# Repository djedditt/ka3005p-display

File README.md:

# ka3005p-display

This repository contains a KiCad project for a Korad KA3005P display driver, included are the schematic, pcb layout and gerber files. This board can replace the existing KA002_V3.x PCB in a Korad KA3005P (or KA3005D) power supply.

## Table of Contents

* [Bill of Materials (BOM)](#bom)
* [Pictures](#pictures)
* [License](#license)
* [Contact](#contact)

## Bill of Materials (BOM)

Below you'll find the bill of materials for this board. The original PCB comes with 4.0mm LEDs, but I went for 5.0mm because those are more readily available.

| ID | Designator | Description | Quantity |
|---|---|---|---|
|1|C1|Capacitor, Ceramic, 22uF, 25V, 10%, X7R, 0805|1|
|2|LED1, LED2|4-Digit 7-Segment LED Display, Red, Common Cathode, TH, 0.40"|2|
|3|R17, R18, R19, R20, R21|Resistor, 1k Ohm, 1%, 1/8 W, 0805|5|
|4|Q4, Q5, Q6, Q7, Q8|NPN Transistor, MMBT3904, SOT-23-3|5|
|5|D1, D2, D3, D4, D5, D6, D7, D8, D9, D10|LED, Red, TH, 4.0mm (or 5.0mm)|10|
|6|U18|Low Dropout Linear Regulator, AZ1117-3.3, SOT-223|1|
|7|R1, R2, R3, R4, R5, R6, R7, R8, R9, R10, R11, R12, R13, R14, R15, R16|Resistor, 330 Ohm, 5%, 1/4 W, 0805|16
|8|U1, U3| 8-Bit Shift Register, 74HC595, SOIC-16|2
|9|CON1| Female Header, 12-Pin (2x6), 2.54mm|1

## Pictures

The finished board:

Bare PCB (front and back):

## License

This work is licensed under a [Creative Commons Attribution 4.0 International
License][cc-by].

[cc-by]: http://creativecommons.org/licenses/by/4.0/ 

## Contact

You can e-mail me at: ![email-address]

[email-address]: https://djedditt.net/github/email-address.gif

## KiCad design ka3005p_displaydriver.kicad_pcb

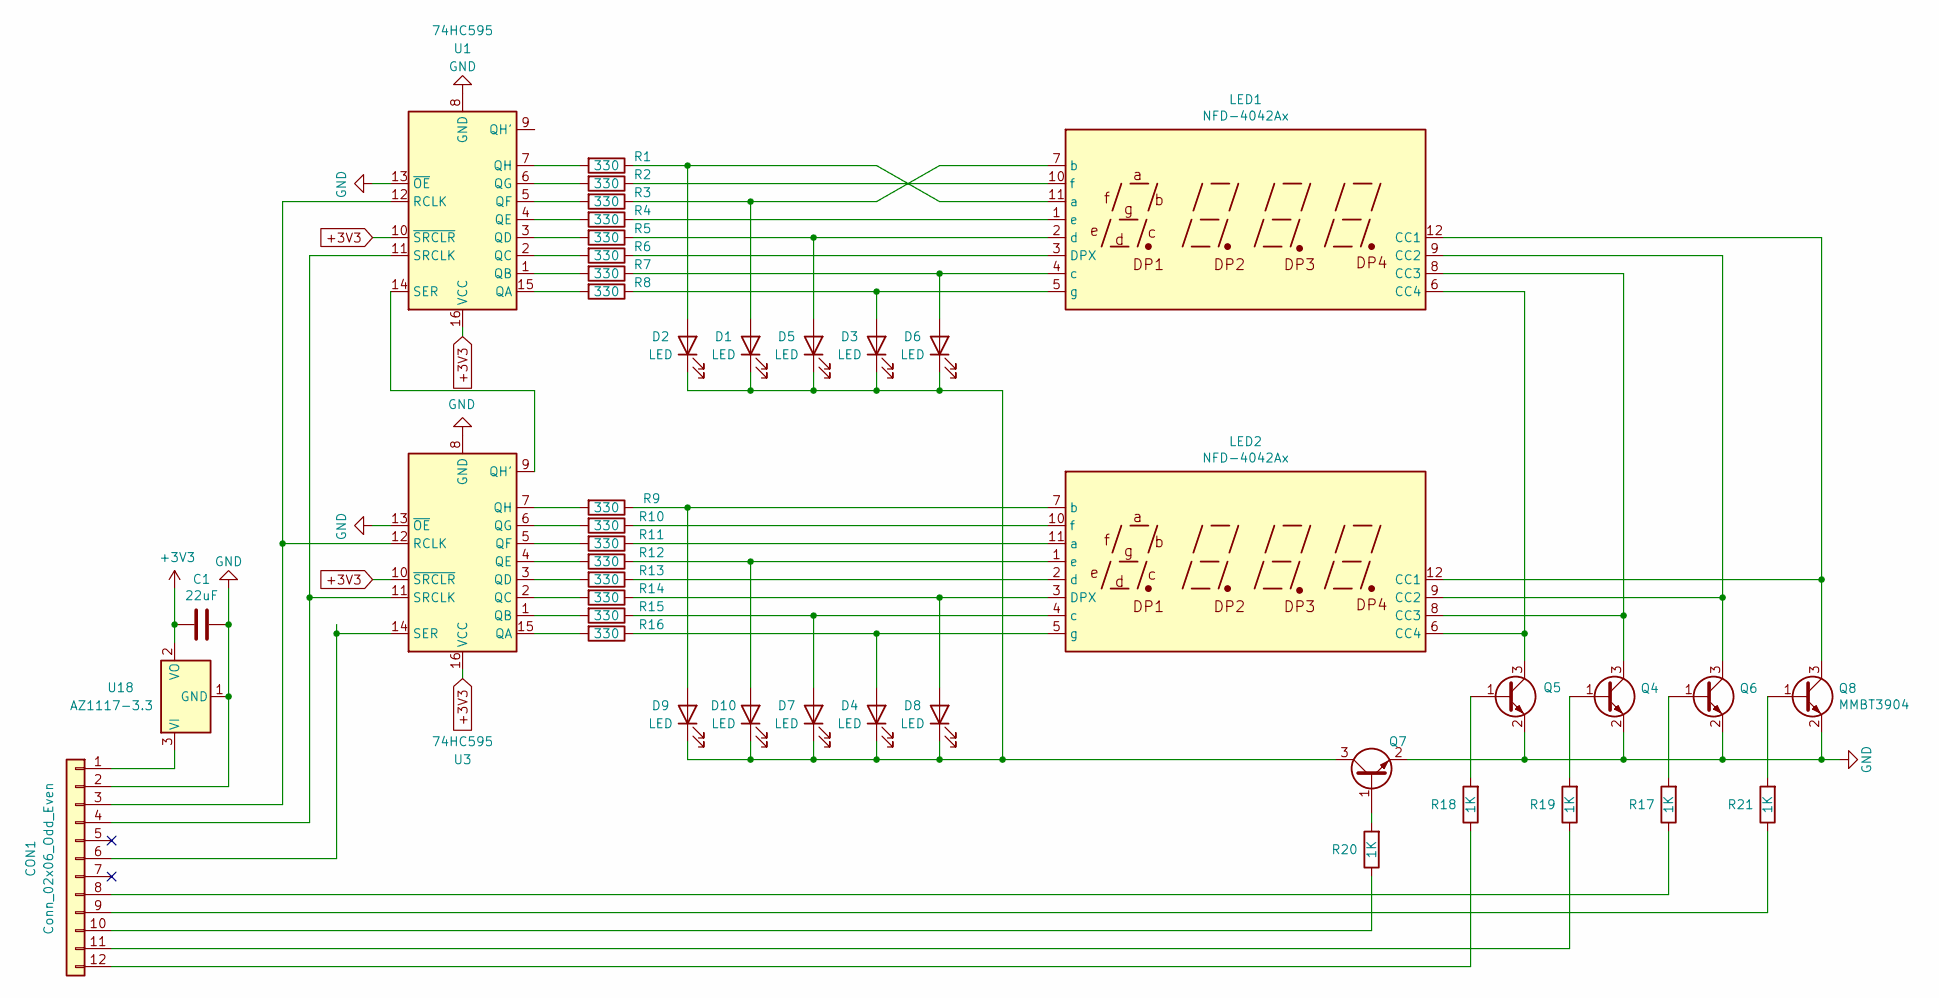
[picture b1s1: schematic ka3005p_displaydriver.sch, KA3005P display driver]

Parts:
C1: 22uF; C_0805_2012Metric_Pad1.15x1.40mm_HandSolder
CON1: Conn_02x06_Odd_Even; PinSocket_2x06_P2.54mm_Vertical
D1, D2, D3, D4, D5, D6, D7, D8, D9, D10: LED; LED_D4.0mm
LED1, LED2: NFD-4042Ax
Q4, Q5, Q6, Q7, Q8: MMBT3904; SOT-23
R1, R2, R3, R4, R5, R6, R7, R8, R9, R10, R11, R12, R13, R14, R15, R16: 330; R_0805_2012Metric_Pad1.15x1.40mm_HandSolder
R17, R18, R19, R20, R21: 1K; R_0805_2012Metric_Pad1.15x1.40mm_HandSolder
U1, U3: 74HC595; SOIC-16_3.9x9.9mm_P1.27mm
U18: AZ1117-3.3; SOT-223

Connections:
+3V3: C1.2, U1.10 (~SRCLR), U1.16 (VCC), U3.10 (~SRCLR), U3.16 (VCC), U18.2 (VO), U18.4
GND: C1.1, CON1.2, Q4.2 (E), Q5.2 (E), Q6.2 (E), Q7.2 (E), Q8.2 (E), U1.8 (GND), U1.13 (~OE), U3.8 (GND), U3.13 (~OE), U18.1 (GND)
unnamed: CON1.1, U18.3 (VI)
unnamed: CON1.3, U1.12 (RCLK), U3.12 (RCLK)
unnamed: CON1.4, U1.11 (SRCLK), U3.11 (SRCLK)
unnamed: CON1.6, U3.14 (SER)
unnamed: CON1.8, R17.1
unnamed: CON1.9, R21.1
unnamed: CON1.10, R20.1
unnamed: CON1.11, R19.1
unnamed: CON1.12, R18.1
unnamed: D1.1 (K), D2.1 (K), D3.1 (K), D4.1 (K), D5.1 (K), D6.1 (K), D7.1 (K), D8.1 (K), D9.1 (K), D10.1 (K), Q7.3 (C)
unnamed: D1.2 (A), LED1.7 (b), R3.1
unnamed: D2.2 (A), LED1.11 (a), R1.1
unnamed: D3.2 (A), LED1.5 (g), R8.1
unnamed: D4.2 (A), LED2.5 (g), R16.1
unnamed: D5.2 (A), LED1.2 (d), R5.1
unnamed: D6.2 (A), LED1.4 (c), R7.1
unnamed: D7.2 (A), LED2.4 (c), R15.1
unnamed: D8.2 (A), LED2.3 (DPX), R14.1
unnamed: D9.2 (A), LED2.7 (b), R9.1
unnamed: D10.2 (A), LED2.1 (e), R12.1
unnamed: LED1.1 (e), R4.1
unnamed: LED1.3 (DPX), R6.1
unnamed: LED1.6 (CC4), LED2.6 (CC4), Q5.3 (C)
unnamed: LED1.8 (CC3), LED2.8 (CC3), Q4.3 (C)
unnamed: LED1.9 (CC2), LED2.9 (CC2), Q6.3 (C)
unnamed: LED1.10 (f), R2.1
unnamed: LED1.12 (CC1), LED2.12 (CC1), Q8.3 (C)
unnamed: LED2.2 (d), R13.1
unnamed: LED2.10 (f), R10.1
unnamed: LED2.11 (a), R11.1
unnamed: Q4.1 (B), R19.2
unnamed: Q5.1 (B), R18.2
unnamed: Q6.1 (B), R17.2
unnamed: Q7.1 (B), R20.2
unnamed: Q8.1 (B), R21.2
unnamed: R1.2, U1.7 (QH)
unnamed: R2.2, U1.6 (QG)
unnamed: R3.2, U1.5 (QF)
unnamed: R4.2, U1.4 (QE)
unnamed: R5.2, U1.3 (QD)
unnamed: R6.2, U1.2 (QC)
unnamed: R7.2, U1.1 (QB)
unnamed: R8.2, U1.15 (QA)
unnamed: R9.2, U3.7 (QH)
unnamed: R10.2, U3.6 (QG)
unnamed: R11.2, U3.5 (QF)
unnamed: R12.2, U3.4 (QE)
unnamed: R13.2, U3.3 (QD)
unnamed: R14.2, U3.2 (QC)
unnamed: R15.2, U3.1 (QB)
unnamed: R16.2, U3.15 (QA)
unnamed: U1.14 (SER), U3.9 (QH')

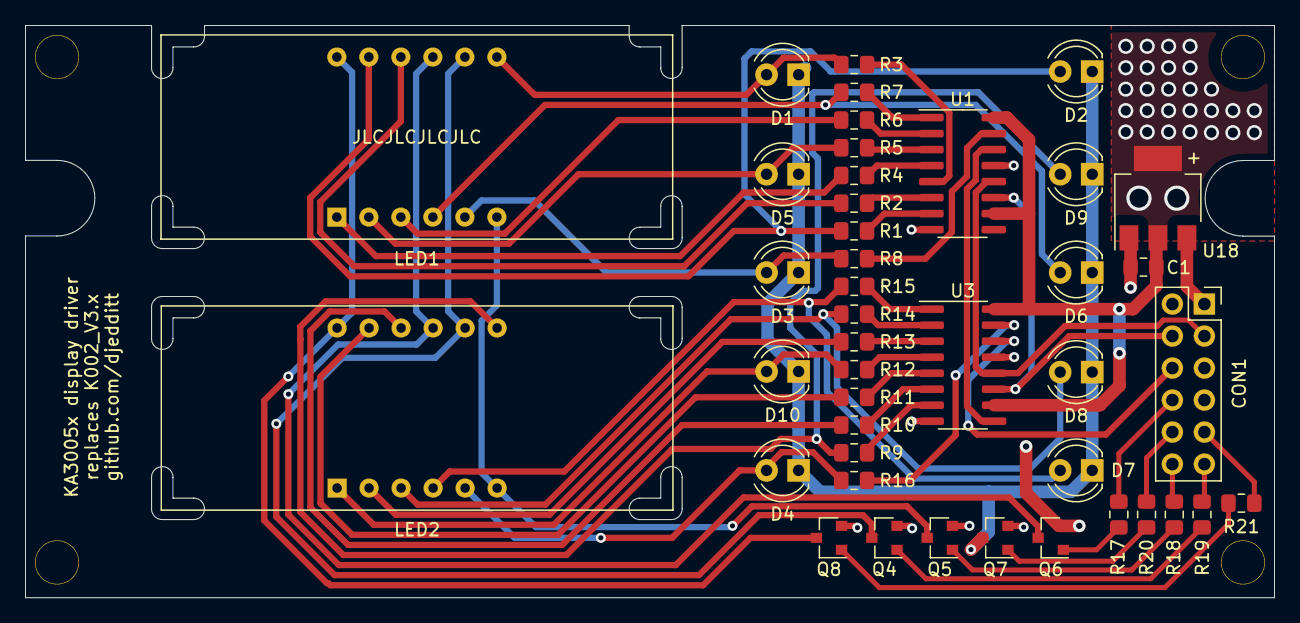
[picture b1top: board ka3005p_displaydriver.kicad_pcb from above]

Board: 2 copper layers, 99.1 x 45.4 mm, 43 parts (0 on the bottom side), 54 nets.

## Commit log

2020-10-09 Fixed github repository URL in schematic
